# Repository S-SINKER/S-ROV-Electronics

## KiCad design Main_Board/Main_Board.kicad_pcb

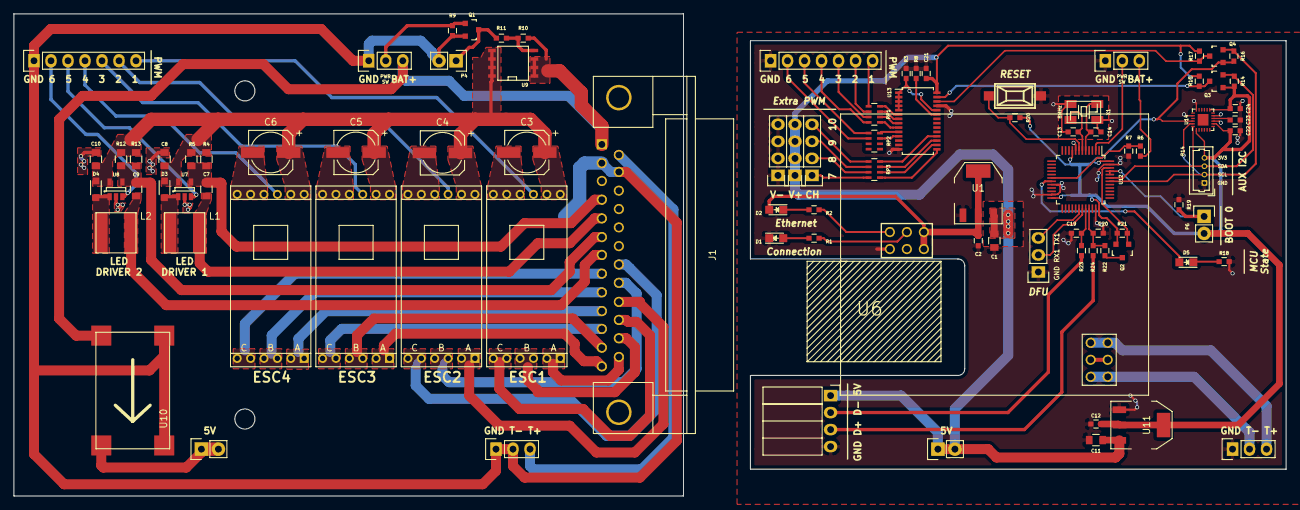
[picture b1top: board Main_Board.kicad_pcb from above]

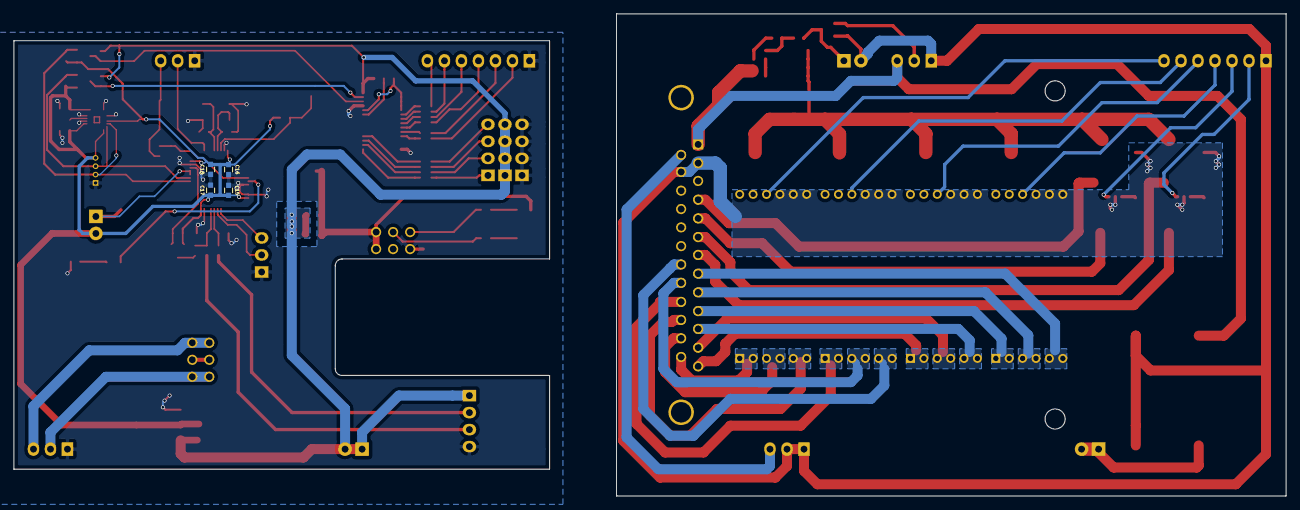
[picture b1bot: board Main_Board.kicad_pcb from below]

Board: 2 copper layers, 190.0 x 72.0 mm, 95 parts (4 on the bottom side), 86 nets.

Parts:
C1, C11: C; C_0805
C2, C12: C; C_0603
C3, C4, C5, C6: CP1; c_elec_6.3x4.5
C7, C9: 1uF; C_0805
C8, C10: 2.2uF; C_0805
C13, C14: 33uF; C_0603
C15, C16, C17, C18: 1uF; C_0603
C19, C20: 47pF; C_0603
C21: 10uF; C_0603
C22: 10nF; C_0603
C23, C24: 0.1uF; C_0603
D1, D2, D5: LED; LED_0805
D3, D4: BAT20JFILM; SOD-323_HandSoldering
J1: DB25; DB25FC
L1, L2: 33uH; inductor_33uH
P1, P2, P7: CONN_01X04; Socket_Strip_Straight_1x04
P3, P11, P12, P16, P17: CONN_01X03; Socket_Strip_Straight_1x03
P4, P9, P10: CONN_01X02; Socket_Strip_Straight_1x02
P6: BOOT; Socket_Strip_Straight_1x02
P8: CONN_01X04; Socket_Strip_Angled_1x04
P13, P15: CONN_01X07; Socket_Strip_Straight_1x07
P14: CONN_01X04; Molex_PicoBlade_53047-0410_04x1.25mm_Straight
Q1: DMN65D8L; SOT-23
Q2: BSS84; SOT-23
Q3, Q4: BSS138; SOT-23
R1, R2, R18: 330; C_0603
R3, R8, R9, R10, R14, R15, R16, R17, R19, R20, R21: 10k; C_0603
R4, R5, R12, R13: 0.5; C_0805
R6: 20k 1%; C_0603
R7: 102k 1%; C_0603
R11: 1k; C_0603
R22: 1.5k; C_0603
R23, R24: 22; C_0603
RP1, RP2, RP3: 220X4; R_Array_Concave_4x0603
SW1: RESET; smd_push
U1, U11: TLV1117LV33; SOT-223
U2, U3, U4, U5: DYS_mini_ESC; DYS_Mini_ESC
U6: TENDA_P200; Tenda_p200
U7, U8: AL8805W5; SOT-23-5
U9: SI4425DDY; SOIC-8-N
U10: DSN-MINI-360
U12: STM32F103CBT6; LQFP-48_7x7mm_Pitch0.5mm
U13: pca9685; TSSOP-28_4.4x9.7mm_Pitch0.65mm
U14: MPU9250; QFN-24-1EP_3x3mm_Pitch0.4mm
X1: 8MHz; crystal_maple

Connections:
/Bottom_Board/5V: P10.1, P10.2, U10.3
/Bottom_Board/CH1: P15.7, U2.2
/Bottom_Board/CH2: P15.6, U3.2
/Bottom_Board/CH3: P15.5, U4.2
/Bottom_Board/CH4: P15.4, U5.2
/Bottom_Board/CH5: P15.3, U7.3
/Bottom_Board/CH6: P15.2, U8.3
/Bottom_Board/LED1+: C7.1, J1.4, R4.2, R5.2, U7.4
/Bottom_Board/LED1-: C7.2, J1.5, L1.2
/Bottom_Board/LED2+: C9.1, J1.6, R12.2, R13.2, U8.4
/Bottom_Board/LED2-: C9.2, J1.7, L2.2
/Bottom_Board/MOTOR_1A: J1.25, U2.4
/Bottom_Board/MOTOR_1B: J1.24, U2.5
/Bottom_Board/MOTOR_1C: J1.23, U2.6
/Bottom_Board/MOTOR_2A: J1.22, U3.4
/Bottom_Board/MOTOR_2B: J1.21, U3.5
/Bottom_Board/MOTOR_2C: J1.20, U3.6
/Bottom_Board/MOTOR_3A: J1.13, U4.4
/Bottom_Board/MOTOR_3B: J1.12, U4.5
/Bottom_Board/MOTOR_3C: J1.11, U4.6
/Bottom_Board/MOTOR_4A: J1.10, U5.4
/Bottom_Board/MOTOR_4B: J1.9, U5.5
/Bottom_Board/MOTOR_4C: J1.8, U5.6
/Bottom_Board/PWR_SW: P12.2, Q1.1, R9.1
/Bottom_Board/T+: J1.14, P17.3
/Bottom_Board/V_BAT: J1.1, P12.3, R10.1, U9.1, U9.2, U9.3, U10.1
/Bottom_Board/V_PWR: C3.1, C4.1, C5.1, C6.1, C8.1, C10.1, D3.1, D4.1, R4.1, R5.1, R12.1, R13.1, U2.3, U3.3, U4.3, U5.3, U7.5, U8.5, U9.5, U9.6, U9.7, U9.8
/Upper_Board/3V3: C12.1, C15.1, C16.1, C17.1, C18.1, C22.1, C24.1, P6.2, P14.4, Q2.2, Q3.1, Q4.1, R14.1, R16.1, R20.1, R21.2, U11.2, U11.4, U12.9, U12.24, U12.36, U12.48, U14.1, U14.8, U14.13, U14.22
/Upper_Board/3V3_PLC: C2.1, D2.2, U1.2, U1.4, U6.3V3
/Upper_Board/5V: C1.1, C11.1, C21.1, P2.1, P2.2, P2.3, P2.4, P8.1, P9.1, P9.2, R15.1, R17.1, U1.3, U11.3, U13.28
/Upper_Board/ADC: R6.2, R7.1, U12.18
/Upper_Board/BOOT0: P6.1, R19.2, U12.44, U12.45
/Upper_Board/CH1: P13.7, RP1.5
/Upper_Board/CH2: P13.6, RP1.6
/Upper_Board/CH3: P13.5, RP1.7
/Upper_Board/CH4: P13.4, RP1.8
/Upper_Board/CH5: P13.3, RP2.5
/Upper_Board/CH6: P13.2, RP2.6
/Upper_Board/CH7: P1.1, RP3.8
/Upper_Board/CH8: P1.2, RP3.7
/Upper_Board/CH9: P1.3, RP3.6
/Upper_Board/CH10: P1.4, RP3.5
/Upper_Board/D14: P11.2, U12.2
/Upper_Board/D25: P3.2, U12.31
/Upper_Board/D26: P3.3, U12.30
/Upper_Board/D+: P8.3, R24.1
/Upper_Board/D-: P8.2, R23.1
/Upper_Board/DISC: Q2.1, R21.1, U12.46
/Upper_Board/OSC_IN: C14.1, U12.5, X1.2
/Upper_Board/OSC_OUT: C13.1, U12.6, X1.1
/Upper_Board/SCL_3V3: P14.2, Q4.2, R16.2, U12.42, U14.23
/Upper_Board/SCL_5V: Q4.3, R17.2, U13.26
/Upper_Board/SDA_3V3: P14.3, Q3.2, R14.2, U12.43, U14.24
/Upper_Board/SDA_5V: Q3.3, R15.2, U13.27
/Upper_Board/T+: P16.3, U6.T_+
/Upper_Board/T-: P16.2, U6.T_-
/Upper_Board/USBDM: C19.1, R23.2, U12.32
/Upper_Board/USBDP: C20.1, R22.1, R24.2, U12.33
/Upper_Board/U_GND: C1.2, C2.2, C11.2, C12.2, C13.2, C14.2, C15.2, C16.2, C17.2, C18.2, C19.2, C20.2, C21.2, C22.2, C23.2, C24.2, D1.1, P3.1, P7.1, P7.2, P7.3, P7.4, P8.4, P11.1, P13.1, P14.1, P16.1, R3.2, R7.2, R8.2, R18.2, R19.1, SW1.1, U1.1, U6.GND, U11.1, U12.8, U12.20, U12.23, U12.35, U12.47, U13.14, U13.25, U14.9, U14.11, U14.18, U14.20, X1.3
/Upper_Board/V_BAT+: P11.3, R6.1
GNDPWR: C3.2, C4.2, C5.2, C6.2, C8.2, C10.2, J1.2, J1.15, P4.2, P12.1, P15.1, P17.1, P17.2, Q1.2, R9.2, U2.1, U3.1, U4.1, U5.1, U7.2, U8.2, U10.2, U10.4
unnamed: C23.1, U14.10
unnamed: D1.2, R1.2
unnamed: D2.1, R2.2
unnamed: D3.2, L1.1, U7.1
unnamed: D4.2, L2.1, U8.1
unnamed: D5.1, R18.1
unnamed: D5.2, U12.19
unnamed: P4.1, Q1.3, R11.2
unnamed: Q2.3, R22.2
unnamed: R1.1, U6.C
unnamed: R2.1, U6.E
unnamed: R3.1, U13.1, U13.2, U13.3, U13.4, U13.5, U13.24
unnamed: R8.1, U13.23
unnamed: R10.2, R11.1, U9.4
unnamed: R20.2, SW1.2, U12.7
unnamed: RP1.1, U13.9
unnamed: RP1.2, U13.8
unnamed: RP1.3, U13.7
unnamed: RP1.4, U13.6
unnamed: RP2.3, U13.11
unnamed: RP2.4, U13.10
unnamed: RP3.1, U13.15
unnamed: RP3.2, U13.16
unnamed: RP3.3, U13.17
unnamed: RP3.4, U13.18

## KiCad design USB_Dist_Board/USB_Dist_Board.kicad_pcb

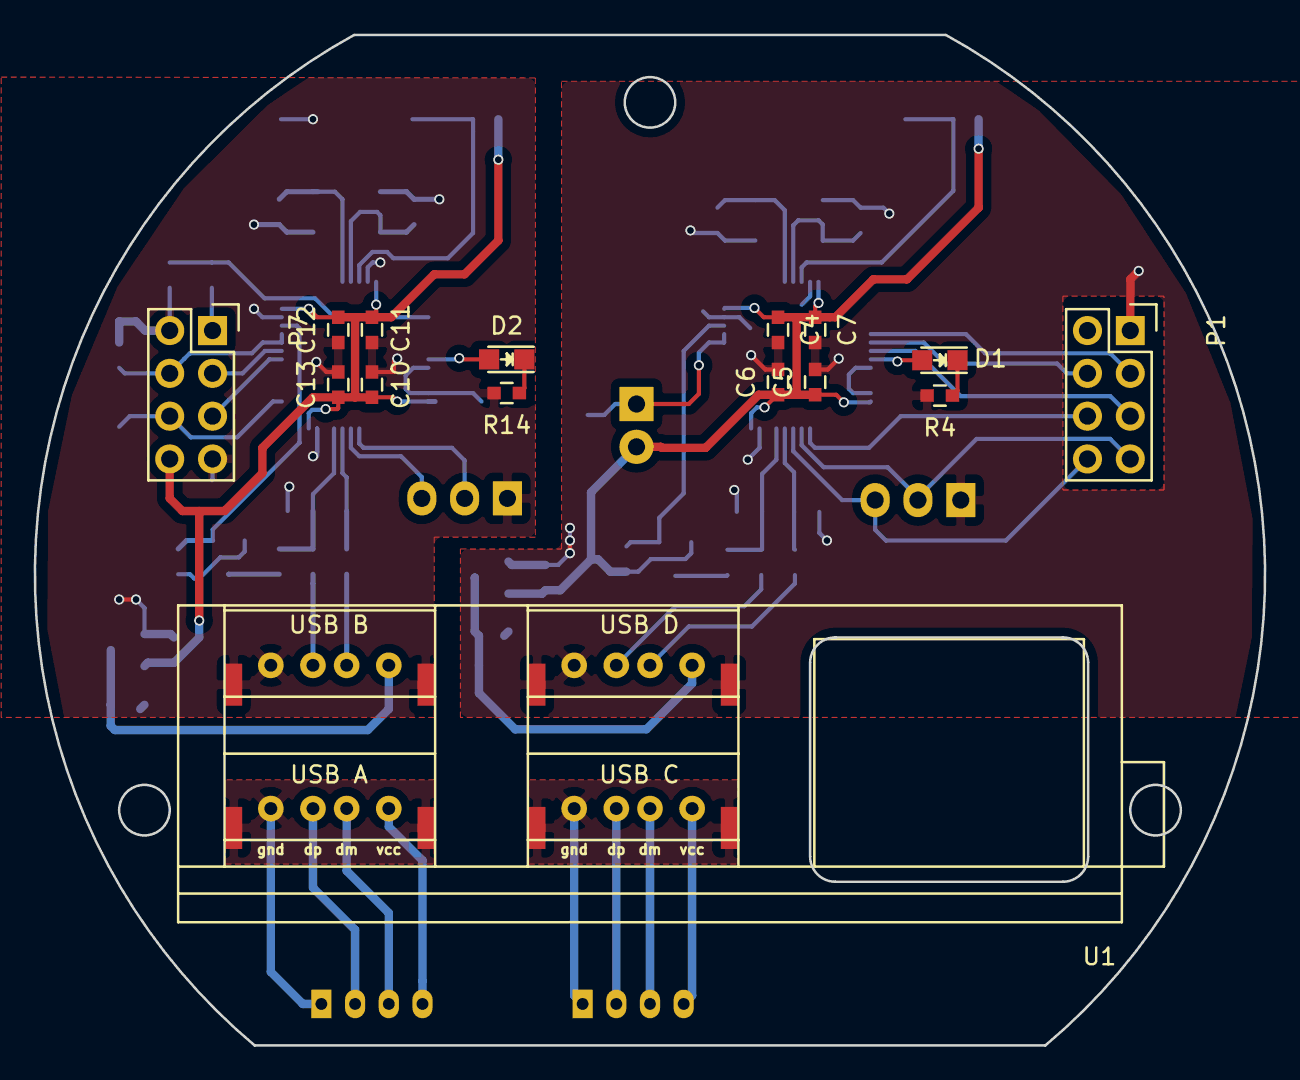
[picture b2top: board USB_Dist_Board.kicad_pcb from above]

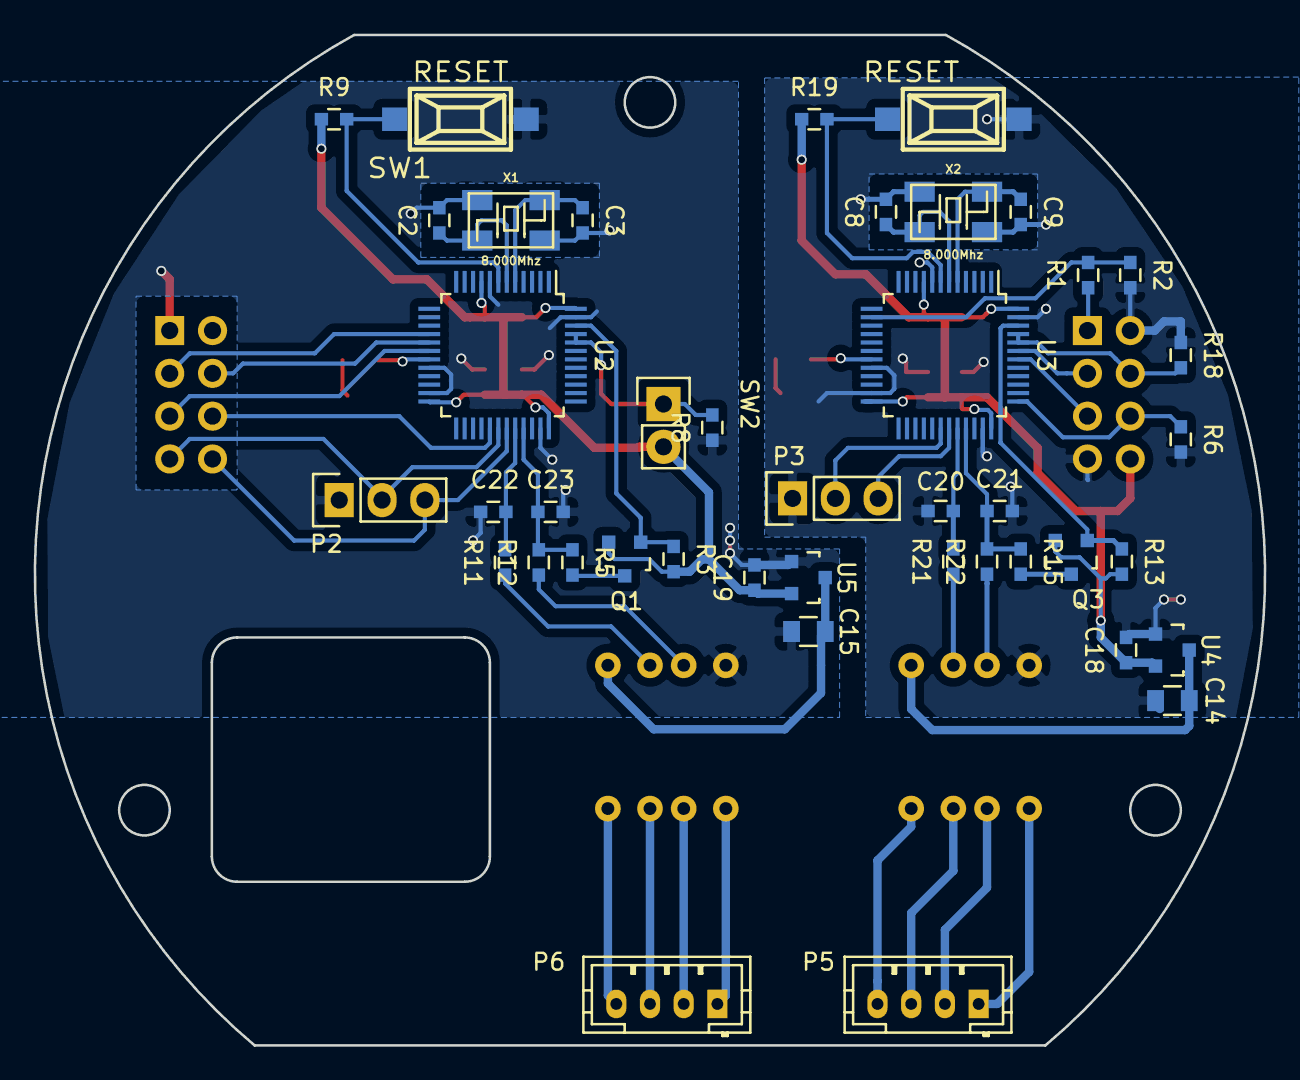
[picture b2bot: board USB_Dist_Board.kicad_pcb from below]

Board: 2 copper layers, 73.0 x 60.0 mm, 57 parts (42 on the bottom side), 51 nets.

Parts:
C2, C3, C8, C9: 26pF; C_0603
C4, C5, C6, C7, C10, C11, C12, C13: 1uF; C_0603
C14, C15: 100uF; C_0805
C18, C19: 10uF; C_0603
C20, C21, C22, C23: 47pF; C_0603
D1, D2: LED; LED_0805
P1, P7: CONN_02X04; Socket_Strip_Straight_2x04
P2, P3: CONN_01X03; Socket_Strip_Straight_1x03
P5, P6: CONN_01X04; JST_PH_B4B-PH-K_04x2.00mm_Straight
Q1, Q3: BSS84; SOT-23
R1, R2, R6: R; C_0603
R3, R8, R9, R13, R18, R19: 10k; C_0603
R4, R14: 330; C_0603
R5, R15: 1.5k; C_0603
R11, R12, R21, R22: 22; C_0603
SW1, SW3: RESET; smd_push
SW2: BOOT; Socket_Strip_Straight_1x02
U1: Raspberry_Front
U2, U3: STM32F103CBT6; LQFP-48_7x7mm_Pitch0.5mm
U4, U5: MCP1703T-3302E; SOT-23
X1, X2: 8.000Mhz; crystal_maple

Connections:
/3V3_A: C4.1, C5.1, C6.1, C7.1, C19.1, Q1.2, R3.2, R9.1, SW2.2, U2.9, U2.24, U2.36, U2.48, U5.2
/3V3_B: C10.1, C11.1, C12.1, C13.1, C18.1, P7.8, Q3.2, R13.2, R19.1, U3.9, U3.24, U3.36, U3.48, U4.2
/ADC1: R1.2, R2.1, U3.14
/BOOT: P7.4, R18.2, U3.44, U3.45
/Maple_mini/BOOT0: R8.2, SW2.1, U2.44, U2.45
/Maple_mini/DISC: Q1.1, R3.1, U2.46
/Maple_mini/OSC_IN: C3.1, U2.5, X1.2
/Maple_mini/OSC_OUT: C2.1, U2.6, X1.1
/Maple_mini/USBDM: C22.1, R11.2, U2.32
/Maple_mini/USBDP: C23.1, R5.1, R12.2, U2.33
/Maple_mini_2/DISC: Q3.1, R13.1, U3.46
/Maple_mini_2/OSC_IN: C9.1, U3.5, X2.2
/Maple_mini_2/OSC_OUT: C8.1, U3.6, X2.1
/Maple_mini_2/RX1: P3.3, U3.31
/Maple_mini_2/TX1: P3.2, U3.30
/Maple_mini_2/USBDM: C20.1, R21.2, U3.32
/Maple_mini_2/USBDP: C21.1, R15.1, R22.2, U3.33
/PWM1: P1.3, U2.16
/PWM2: P1.4, U2.17
/PWM3: P1.5, U2.18
/PWM4: P1.6, U2.29
/PWM5: P1.7, P2.2, U2.30
/PWM6: P1.8, P2.3, U2.31
/PWR_SW: P7.6, R6.1, U3.37
/SCL: P7.5, U3.42
/SDA: P7.3, U3.43
/USB_A_DM: P5.3, U1.3
/USB_A_DP: P5.2, U1.2
/USB_A_GND: P5.1, U1.1, U1.5
/USB_B_DM: R21.1, U1.8
/USB_B_DP: R22.1, U1.7
/USB_B_GND: C8.2, C9.2, C10.2, C11.2, C12.2, C13.2, C14.2, C18.2, C20.2, C21.2, P3.1, P7.2, P7.7, R2.2, R6.2, R14.2, R18.1, SW3.1, U1.6, U1.10, U3.8, U3.20, U3.23, U3.35, U3.47, U4.1, X2.3
/USB_C_DM: P6.3, U1.13
/USB_C_DP: P6.2, U1.12
/USB_C_GND: P6.1, U1.11, U1.15
/USB_D_DM: R11.1, U1.18
/USB_D_DP: R12.1, U1.17
/USB_D_GND: C2.2, C3.2, C4.2, C5.2, C6.2, C7.2, C15.2, C19.2, C22.2, C23.2, P1.1, P2.1, R4.2, R8.1, SW1.1, U1.16, U1.20, U2.8, U2.20, U2.23, U2.35, U2.47, U5.1, X1.3
/VCC_A: P5.4, U1.4
/VCC_B: C14.1, U1.9, U4.3
/VCC_C: P6.4, U1.14
/VCC_D: C15.1, U1.19, U5.3
unnamed: D1.1, R4.1
unnamed: D1.2, U2.19
unnamed: D2.1, R14.1
unnamed: D2.2, U3.19
unnamed: P7.1, R1.1
unnamed: Q1.3, R5.2
unnamed: Q3.3, R15.2
unnamed: R9.2, SW1.2, U2.7
unnamed: R19.2, SW3.2, U3.7

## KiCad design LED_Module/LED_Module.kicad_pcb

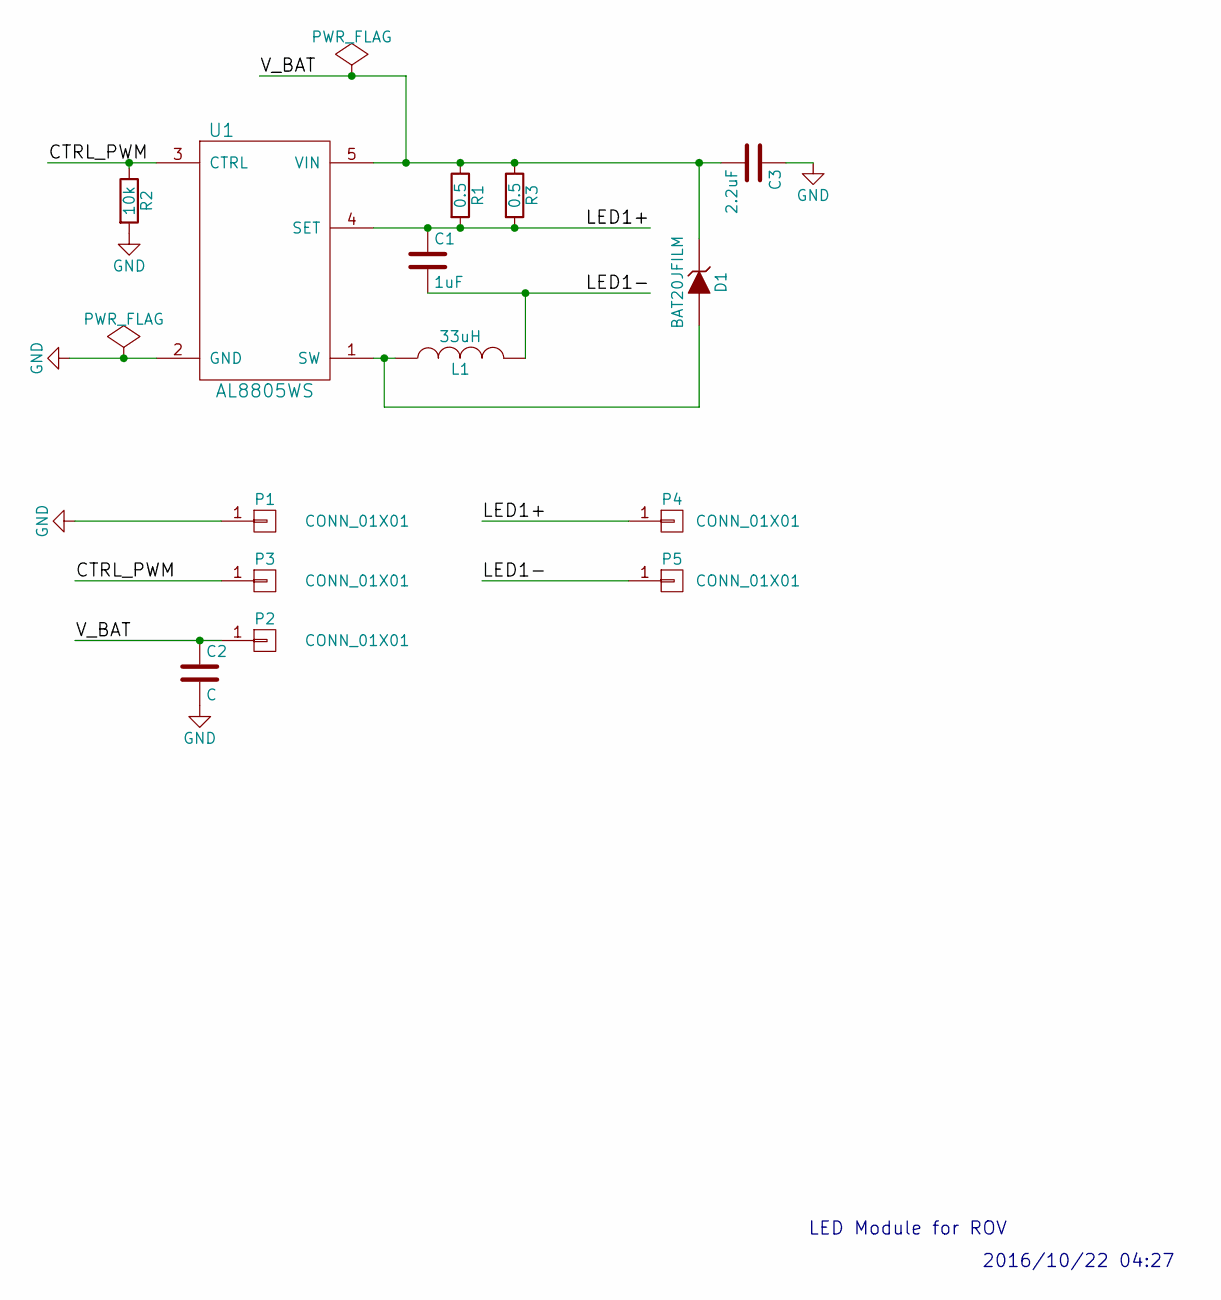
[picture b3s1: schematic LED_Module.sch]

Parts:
C1: 1uF; C_0805_HandSoldering
C2: C; c_elec_5x4.5
C3: 2.2uF; C_0805_HandSoldering
D1: BAT20JFILM; sod323
L1: 33uH; inductor_33uH
P1, P2, P3, P4, P5: CONN_01X01; Socket_Strip_Straight_1x01
R1, R3: 0.5; R_0805_HandSoldering
R2: 10k; R_0805_HandSoldering
U1: AL8805WS; sot23-5

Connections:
/CTRL_PWM: P3.1, R2.1, U1.3 (CTRL)
/LED1+: C1.1, P4.1, R1.2, R3.2, U1.4 (SET)
/LED1-: C1.2, L1.2, P5.1
/V_BAT: C2.1, C3.2, D1.1 (K), P2.1, R1.1, R3.1, U1.5 (VIN)
GND: C2.2, C3.1, P1.1, R2.2, U1.2 (GND)
unnamed: D1.2 (A), L1.1, U1.1 (SW)

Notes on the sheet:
LED Module for ROV
2016/10/22 04:27

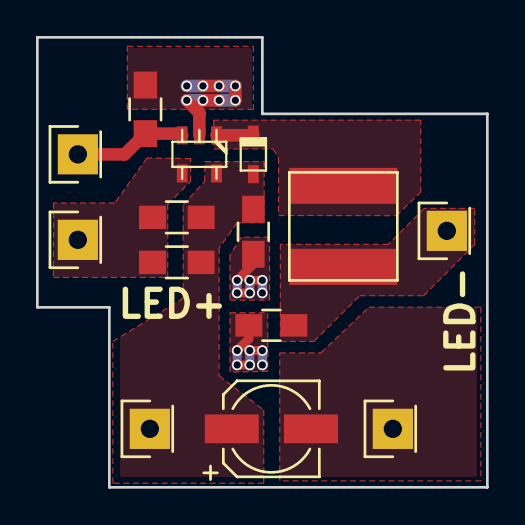
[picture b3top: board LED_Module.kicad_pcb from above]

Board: 2 copper layers, 25.0 x 25.0 mm, 14 parts (0 on the bottom side), 6 nets.

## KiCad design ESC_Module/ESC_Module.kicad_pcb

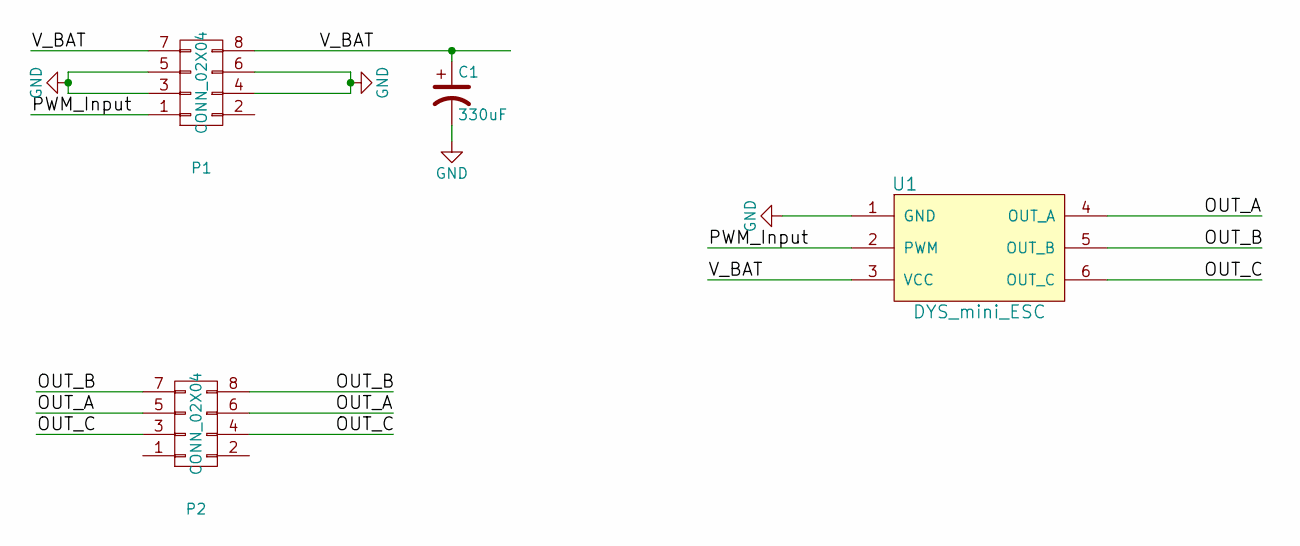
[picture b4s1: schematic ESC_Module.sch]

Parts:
C1: 330uF; c_elec_8x10
P1, P2: CONN_02X04; Socket_Strip_Angled_2x04; Part # 5810
U1: DYS_mini_ESC; DYS_Mini_ESC

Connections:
/OUT_A: P2.5, P2.6, U1.4 (OUT_A)
/OUT_B: P2.7, P2.8, U1.5 (OUT_B)
/OUT_C: P2.3, P2.4, U1.6 (OUT_C)
/PWM_Input: P1.1, U1.2 (PWM)
/V_BAT: C1.1, P1.7, P1.8, U1.3 (VCC)
GND: C1.2, P1.3, P1.4, P1.5, P1.6, U1.1 (GND)

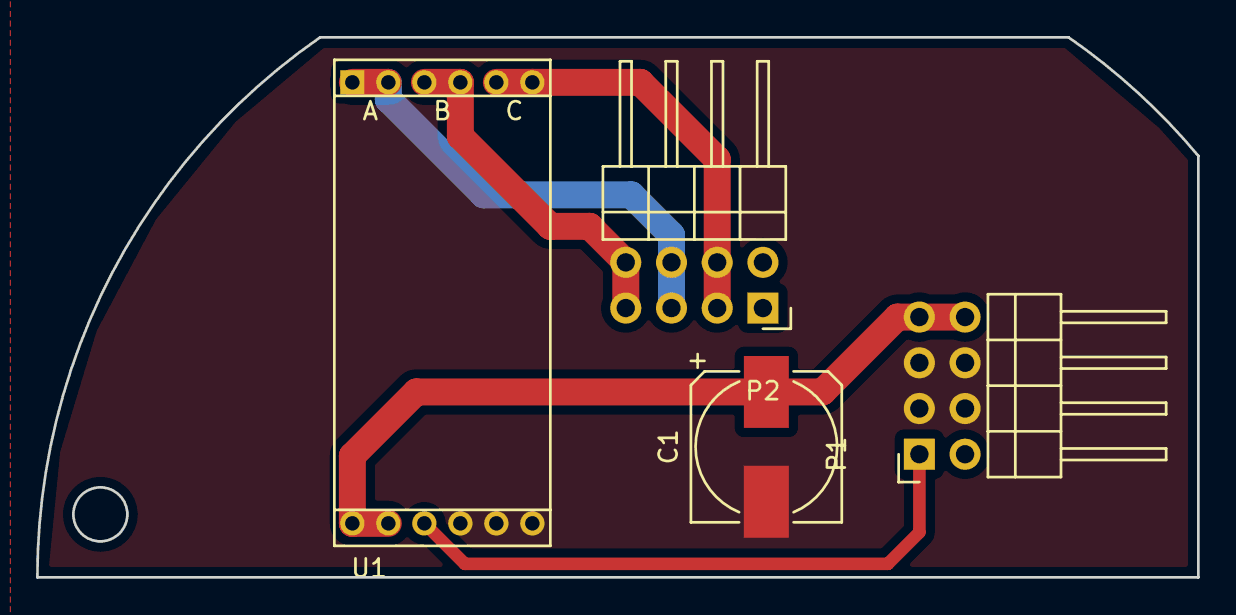
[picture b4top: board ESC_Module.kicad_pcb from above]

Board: 2 copper layers, 64.5 x 30.0 mm, 4 parts (0 on the bottom side), 6 nets.

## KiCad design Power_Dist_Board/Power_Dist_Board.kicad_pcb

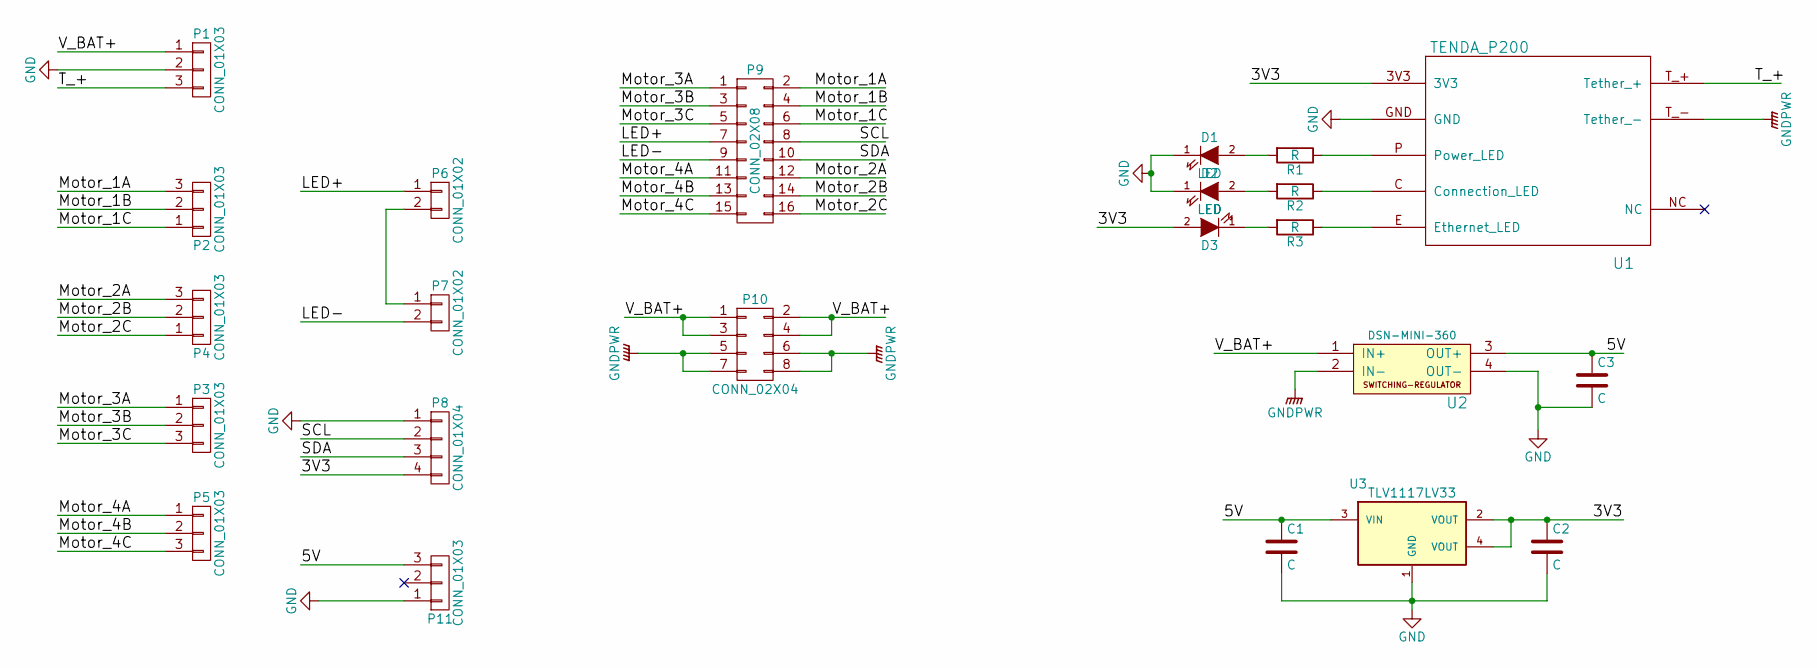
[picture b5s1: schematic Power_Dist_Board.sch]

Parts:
C1: C; C_0805
C2: C; C_0603
C3: C; c_elec_6.3x4.5
D1, D2, D3: LED; LED_0805
P1, P2, P3, P4, P5: CONN_01X03; JST_XH_B03B-XH-A_03x2.50mm_Straight
P6, P7: CONN_01X02; JST_XH_B02B-XH-A_02x2.50mm_Straight
P8: CONN_01X04; JST_XH_B04B-XH-A_04x2.50mm_Straight
P9: CONN_02X08; Socket_Strip_Straight_2x08
P10: CONN_02X04; Socket_Strip_Straight_2x04
P11: CONN_01X03; Socket_Strip_Straight_1x03
R1, R2, R3: R; C_0603
U1: TENDA_P200; Tenda_p200
U2: DSN-MINI-360
U3: TLV1117LV33; SOT-223

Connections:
/3V3: C2.1, D3.2 (A), P8.4, U1.3V3, U3.2 (VOUT), U3.4 (VOUT)
/5V: C1.1, C3.1, P11.3, U2.3 (OUT+), U3.3 (VIN)
/LED+: P6.1, P9.7
/LED-: P7.2, P9.9
/Motor_1A: P2.3, P9.2
/Motor_1B: P2.2, P9.4
/Motor_1C: P2.1, P9.6
/Motor_2A: P4.3, P9.12
/Motor_2B: P4.2, P9.14
/Motor_2C: P4.1, P9.16
/Motor_3A: P3.1, P9.1
/Motor_3B: P3.2, P9.3
/Motor_3C: P3.3, P9.5
/Motor_4A: P5.1, P9.11
/Motor_4B: P5.2, P9.13
/Motor_4C: P5.3, P9.15
/SCL: P8.2, P9.8
/SDA: P8.3, P9.10
/T_+: P1.3, U1.T_+ (Tether_+)
/V_BAT+: P1.1, P10.1, P10.2, P10.3, P10.4, U2.1 (IN+)
GND: C1.2, C2.2, C3.2, D1.1 (K), D2.1 (K), P1.2, P8.1, P11.1, U1.GND, U2.4 (OUT-), U3.1 (GND)
GNDPWR: P10.5, P10.6, P10.7, P10.8, U1.T_- (Tether_-), U2.2 (IN-)
unnamed: D1.2 (A), R1.2
unnamed: D2.2 (A), R2.2
unnamed: D3.1 (K), R3.2
unnamed: P6.2, P7.1
unnamed: R1.1, U1.P (Power_LED)
unnamed: R2.1, U1.C (Connection_LED)
unnamed: R3.1, U1.E (Ethernet_LED)

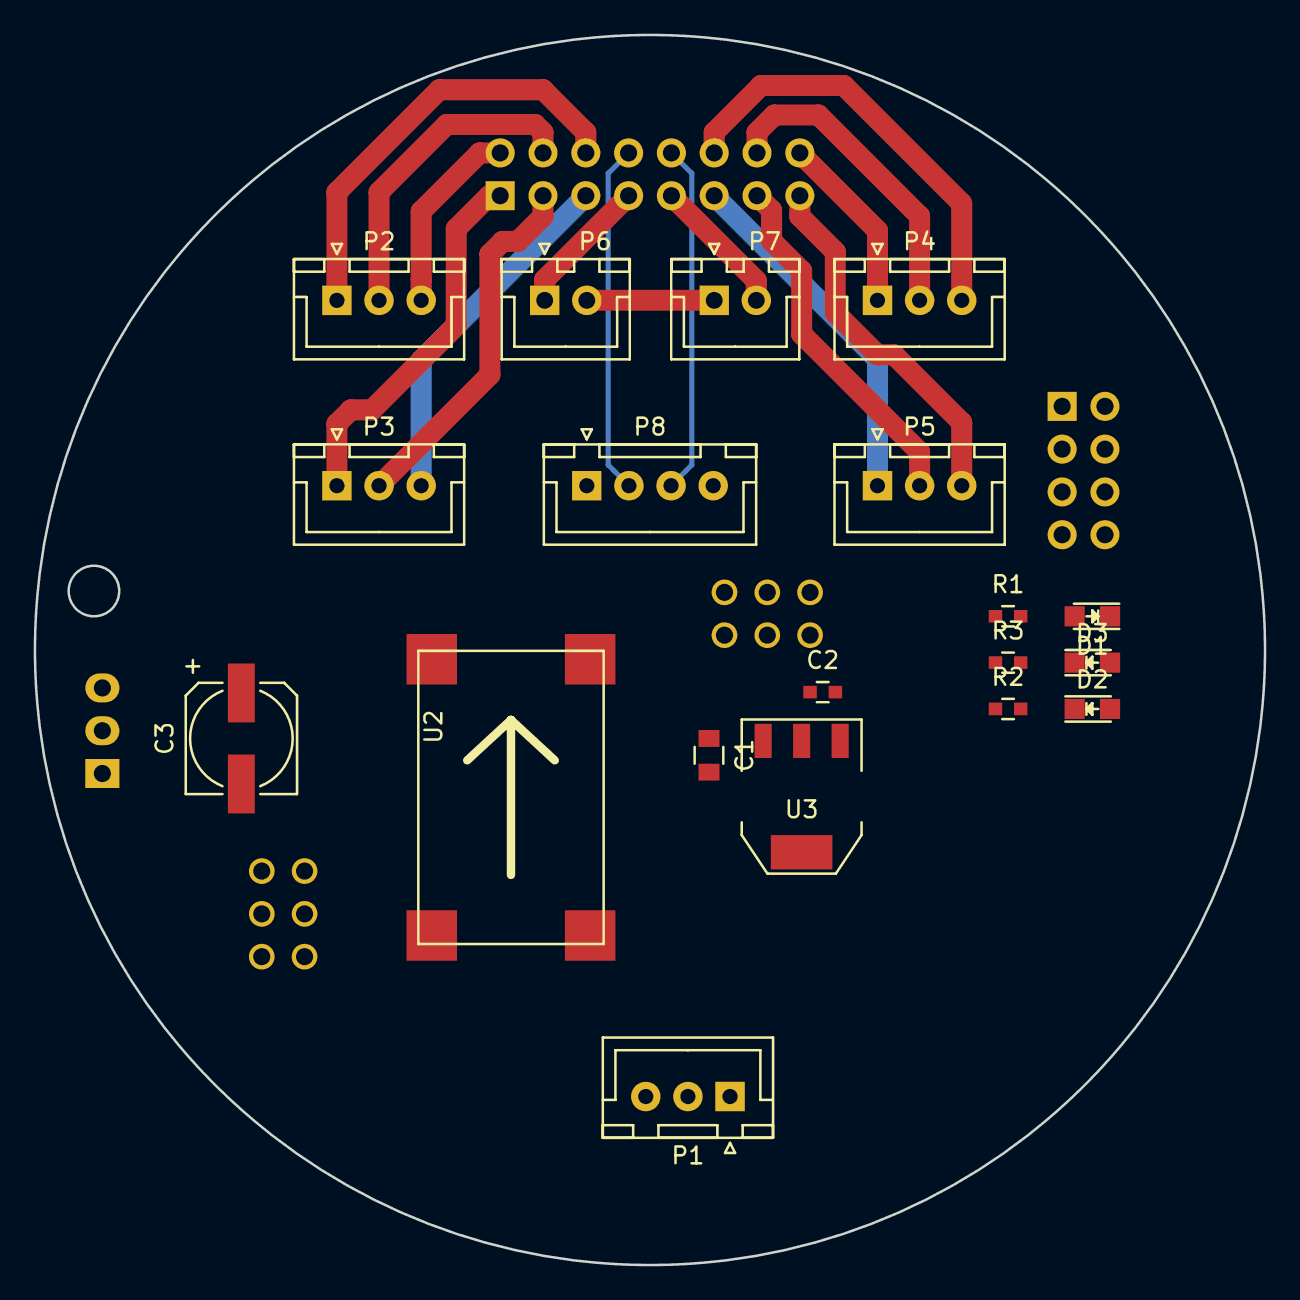
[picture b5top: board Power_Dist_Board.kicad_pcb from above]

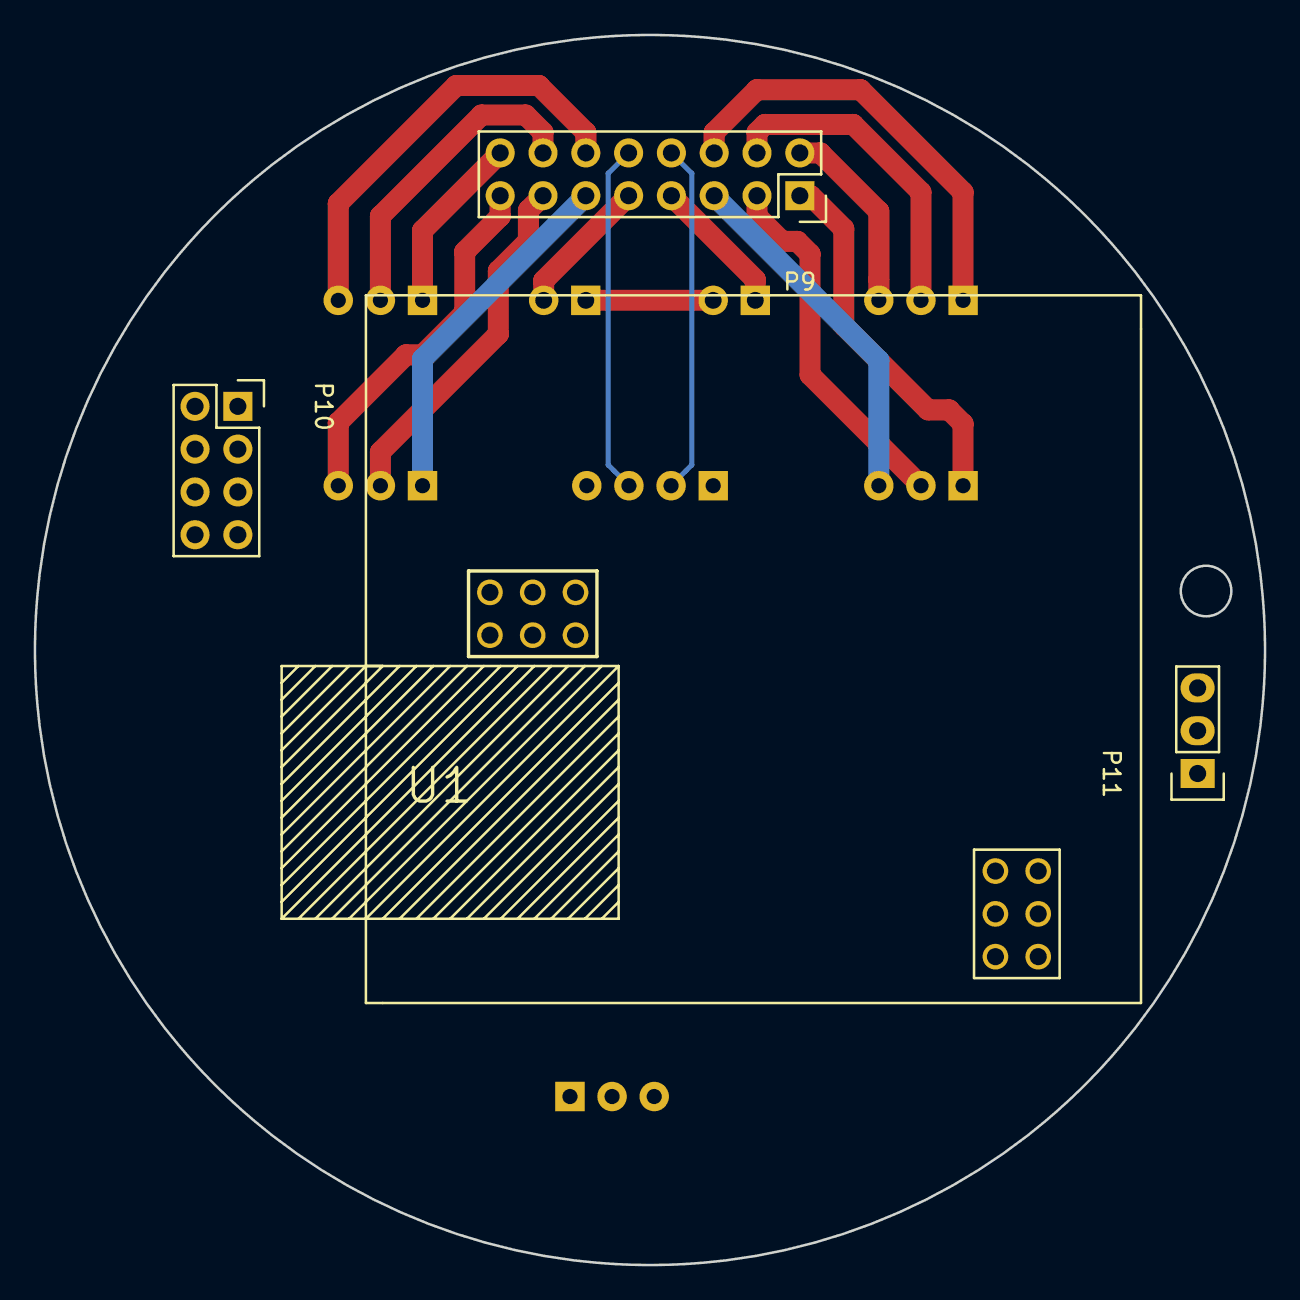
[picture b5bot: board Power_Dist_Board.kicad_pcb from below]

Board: 2 copper layers, 73.0 x 73.0 mm, 23 parts (4 on the bottom side), 29 nets.

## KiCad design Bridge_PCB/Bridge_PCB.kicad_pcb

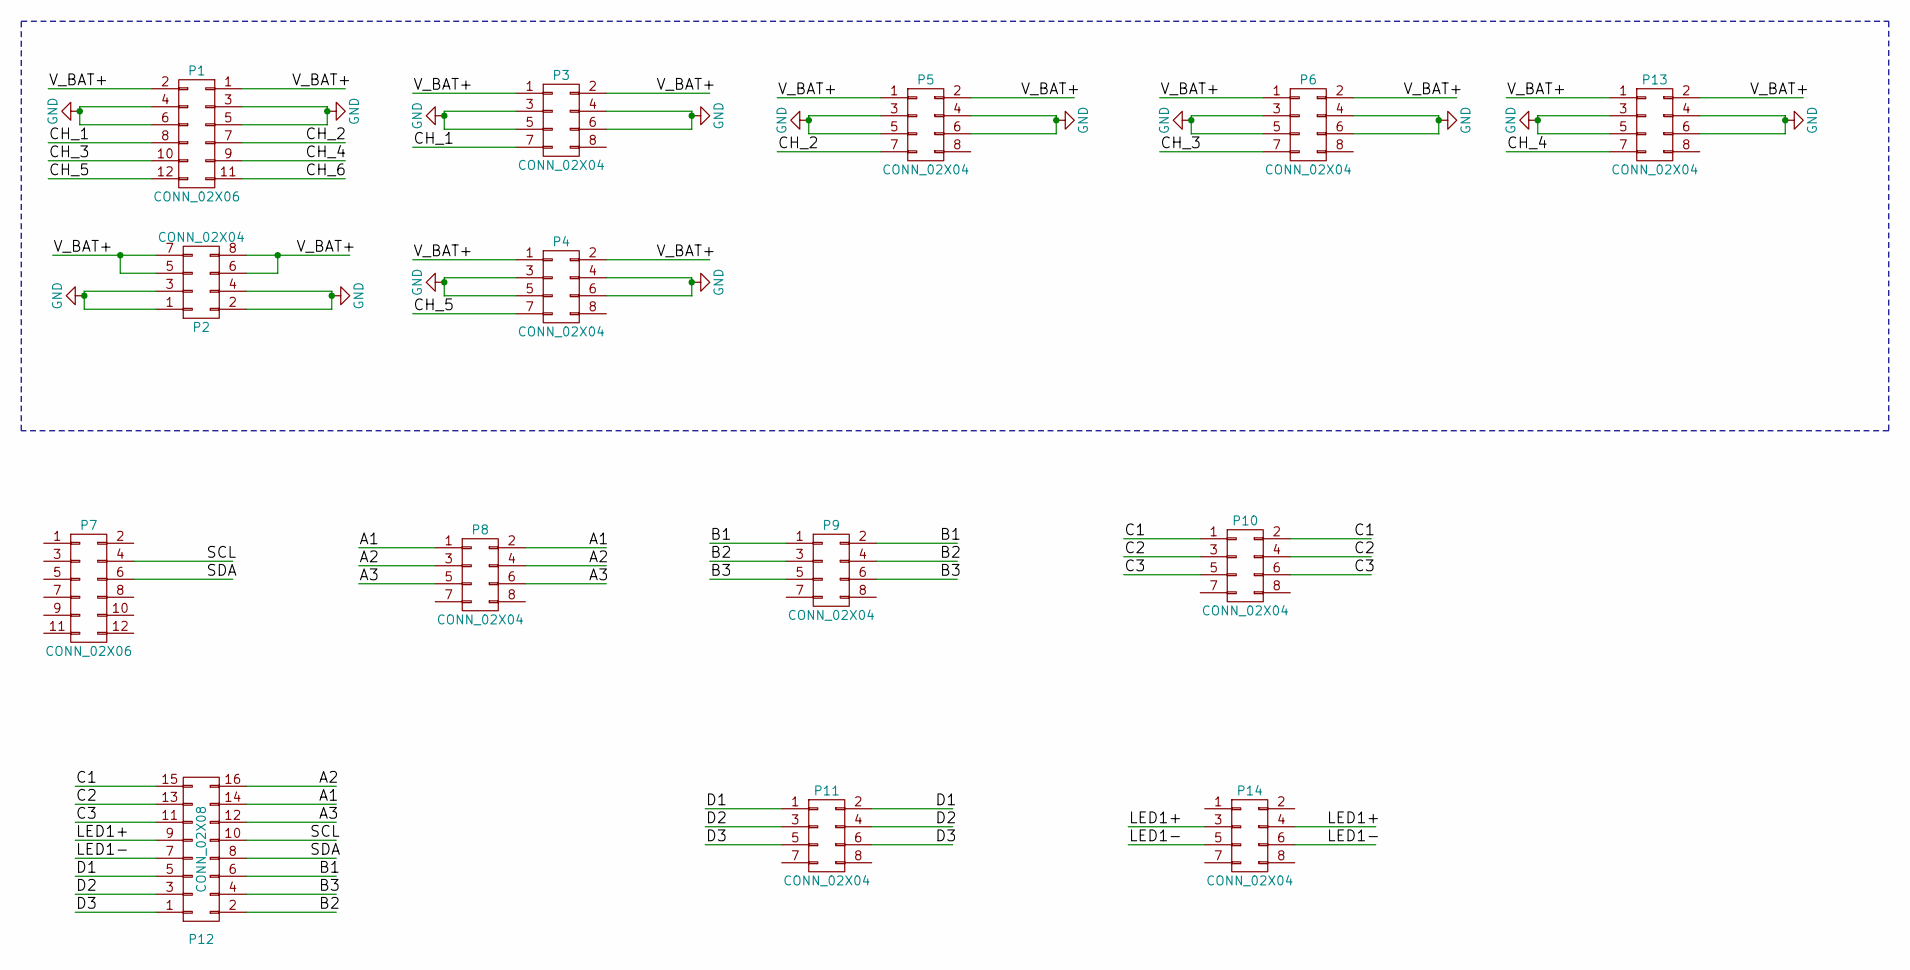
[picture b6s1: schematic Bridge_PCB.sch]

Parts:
P1, P7: CONN_02X06; FCI 68021-412HLF_02x06
P2: CONN_02X04; Socket_Strip_Angled_2x04
P3, P4, P5, P6, P8, P9, P10, P11, P13, P14: CONN_02X04; Socket_Strip_Straight_2x04
P12: CONN_02X08; Socket_Strip_Angled_2x08

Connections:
/A1: P8.1, P8.2, P12.14
/A2: P8.3, P8.4, P12.16
/A3: P8.5, P8.6, P12.12
/B1: P9.1, P9.2, P12.6
/B2: P9.3, P9.4, P12.2
/B3: P9.5, P9.6, P12.4
/C1: P10.1, P10.2, P12.15
/C2: P10.3, P10.4, P12.13
/C3: P10.5, P10.6, P12.11
/CH_1: P1.8, P3.7
/CH_2: P1.7, P5.7
/CH_3: P1.10, P6.7
/CH_4: P1.9, P13.7
/CH_5: P1.12, P4.7
/D1: P11.1, P11.2, P12.5
/D2: P11.3, P11.4, P12.3
/D3: P11.5, P11.6, P12.1
/LED1+: P12.9, P14.3, P14.4
/LED1-: P12.7, P14.5, P14.6
/SCL: P7.4, P12.10
/SDA: P7.6, P12.8
/V_BAT+: P1.1, P1.2, P2.5, P2.6, P2.7, P2.8, P3.1, P3.2, P4.1, P4.2, P5.1, P5.2, P6.1, P6.2, P13.1, P13.2
GND: P1.3, P1.4, P1.5, P1.6, P2.1, P2.2, P2.3, P2.4, P3.3, P3.4, P3.5, P3.6, P4.3, P4.4, P4.5, P4.6, P5.3, P5.4, P5.5, P5.6, P6.3, P6.4, P6.5, P6.6, P13.3, P13.4, P13.5, P13.6

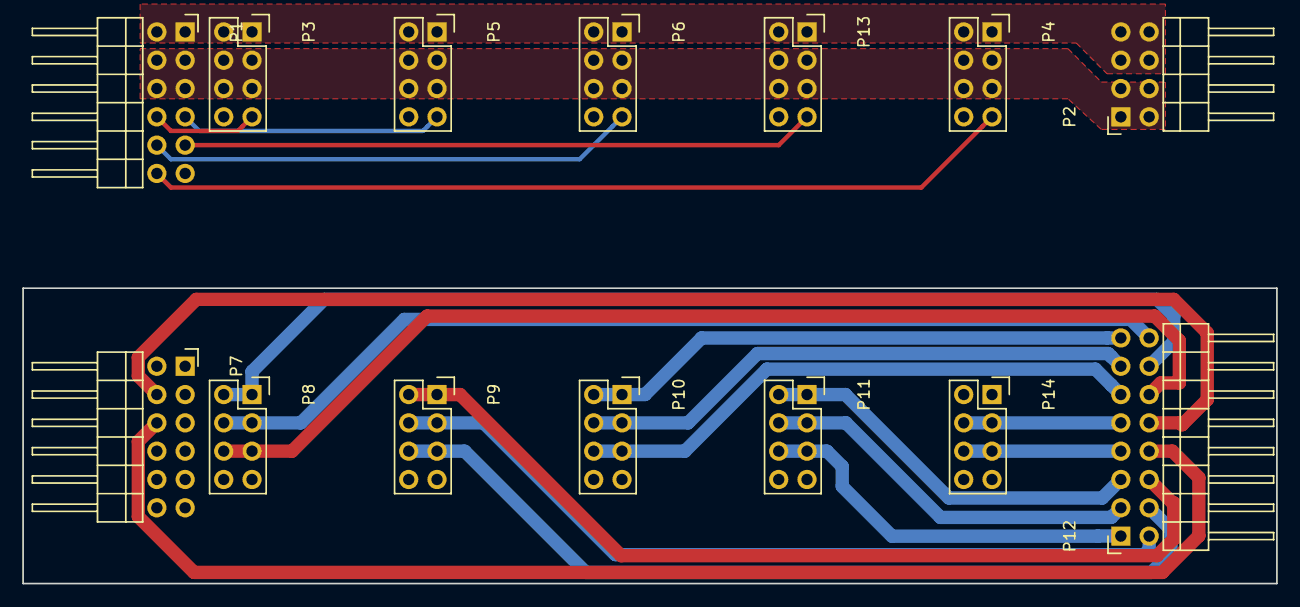
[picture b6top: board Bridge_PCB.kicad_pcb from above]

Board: 2 copper layers, 112.5 x 26.5 mm, 14 parts (0 on the bottom side), 23 nets.

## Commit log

2016-11-05 Resize PCBs
2016-11-05 Add Power Distribution Board
2016-11-05 Commit update
2016-11-07 modify..
2016-11-07 Recover LED_Module project
2016-11-09 LED Modulization
2016-11-10 PCB square shape
2016-11-11 Resize LED module
2016-11-11 LED Module Routing
2016-11-12 LED-MODULE : resize pad
2016-11-13 LED Module PWM pull down
2016-11-13 Add Main Board project & Delete ESC Module
2016-11-13 Main Module update
2016-11-13 Main Board update
2016-11-14 USB_Dist_Board change pin map
2016-11-14 Main Board : Add Braket Hole
2016-11-14 Add Braket_PCB Project
2016-11-14 Main Board & USB Board : Edit EdgeCuts
2016-11-16 Main Board incomplete routing
2016-11-17 Main Board : Separate PCB into two part
2016-11-17 Main Board : Recover LED driver USB Dist Board : Delete ADC voltage divider
2016-11-19 development start
2016-11-19 shit
2016-11-21 Final Routing
2016-11-21 Schematic arrangement
